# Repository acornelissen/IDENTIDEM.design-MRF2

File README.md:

# IDENTIDEM.design M(edium Format) (R)ange(F)inder Two (MRF2)

MRF2 is version two of an open hardware / open firmware medium-format rangefinder camera for **Mamiya Press / Universal Press lenses**. It combines custom PCBs, ESP32-S3 firmware, LiDAR-based lens coupled focusing, dual OLED displays, and printed mechanical parts so you can build a fully featured medium-format shooter with configurable lens profiles and film formats.

It is based on the [Panomicron Thulium](https://www.panomicron.com/thulium) designed by Oscar Oweson, has been heavily modified, but has kept the best ideas from that camera.

Keep checking back regularly as I keep making improvements as I use my own copy of this camera. 
You can [support me on Patreon](https://patreon.com/IDENTIDEMdesign), or just show me your builds and the photos you're making with the camera!

## Repo at a Glance

- `Firmware/` – ESP32-S3 Arduino firmware (full details in `Firmware/README.md`)
- `PCBs/` – KiCad projects + production Gerbers, in two supported revisions (see **Which board version?** below):
  - `PCBs/v2.0/` (MRF-Pro-v8) – adds a dedicated low-noise LiDAR regulator on the breakout, and reworks the main board's FPC power delivery and switch: v1 feeds the breakout one switched 3.3 V rail on FPC pins 1 and 6; v2 gives the LDO its own `VBAT` feed on pin 1 and adds full deterministic shutdown.
  - `PCBs/v1.0/` (MRF-Pro-v7.5) – simpler boards; great for short-range and landscape use.
  - Each revision holds `Main PCB/` (main board) and `Breakout/` (sensor breakout) sub-folders.
- `3MF/` – Print-ready 3MF files organized by part type (body, accessories, masks, fine parts)
- `STEP & F3D/` – Full assembly CAD (`MRF2-complete.f3d`) and shared STEP export (`MRF2-complete.step`)
- `OrcaSlicer/` – Slicer project files/profiles for printing

## Documentation Index

- `Documentation/flash-firmware/README.md` – Building and flashing the firmware on macOS, Linux, and Windows (VS Code or CLI)
- `Documentation/web-updater/README.md` – GitHub Pages browser updater architecture and deployment
- `Documentation/user-manual/USER_MANUAL.md` – On-device UI and calibration user manual
- `Documentation/wiring/README.md` – Power-switch/buttons and breakout-to-LiDAR harness wiring diagrams, for both board revisions
- `Firmware/README.md` – Firmware architecture, configuration, and CLI build commands

## Camera Features

- "LiDAR" distance measurement for accurate focus
- Dual OLED UI: 128×128 main in-viewfinder display + 128×32 external status display
- Light meter & exposure calculation for multiple ISO values
- Lens coupled via a high-accuracy linear position sensor
- Electronic frame counting using a rotary encoder
- Battery monitoring and on-device configuration, like in-camera lens calibration

## Which board version: v1 or v2?

Two board revisions are supported, and **the latest firmware runs on both, unchanged** — there are no board-specific builds, pin maps, or config flags. Connectors, sensors, displays, optics, printed parts, and the main board's component placement and outline are common to both, **but the main board's LiDAR power delivery was significantly reworked, alongside the breakout hardware.** On v1 the breakout runs entirely off one rail: the Feather's 3.3 V leaves the main board through the J4 power switch and comes back on FPC pins 1 and 6, so the LiDAR's laser supply, its logic supply and the STEMMA QT bus all hang off the same undecoupled net. That is the laser-pulse brownout this respin fixes. v2 splits the rails: pin 1 carries `VBAT` straight to the breakout's own LDO, and pin 6 stays the switched `3.3OUT` that gates it. Choose by the LiDAR range you need:

| | **v1 — MRF-Pro-v7.5** (`PCBs/v1.0/`) | **v2 — MRF-Pro-v8** (`PCBs/v2.0/`) |
| --- | --- | --- |
| Breakout | Bare — just the three connectors | Same connectors **+ a dedicated LiDAR LDO** (8 extra SMD parts) |
| FPC power delivery (main board) | One rail for everything: switched Feather 3.3 V on **both** pins 1 and 6 | Two rails: pin 1 carries **`VBAT`** to the breakout's LDO, pin 6 carries the gated, switched **`3.3OUT`** that enables it |
| LiDAR power | Shared Feather 3.3 V rail, no decoupling at the sensor | Isolated low-noise 3.3 V regulated **at the sensor** (TLV75533 off VBAT) |
| LiDAR range | Good up close and at landscape distance; **falls off at mid distance and in bright ambient** | **Full rated range indoors and in shade; direct sun still caps range** (~3 m on a sunlit target — a sensor optics limitation, not power-related; no board revision or firmware fixes it) |
| Power switch (main board) | Basic on/off — single shared 3.3 V net through J4 | Reworked **J4 DPDT**, two independent poles (gate `3.3OUT`; hold MCU `EN` low) for full deterministic shutdown (≤1 µA off) — same connector, board outline, and component placement, traces rerouted |
| Build effort | **Lowest** — breakout is a bare board, no SMD assembly | A bit more — breakout is an SMD assembly job (JLCPCB BOM/CPL provided) |
| Best for | Portraits ~1–3 m and landscapes; the cheapest, easiest build | Full-range focus indoors and in shade, better (not unlimited) in direct sun — the fuller-featured build |

- **Pick v1** for the simplest, cheapest build if you mostly shoot within a few metres or at landscape distances. Its LiDAR range can still be improved with the [hand-solder decoupling stopgap](Documentation/hardware-errata/lidar-stage1-decoupling.md), a v1-only remedy that v2 builds in.
- **Pick v2** for the sensor's full distance range indoors and in shade, deterministic power-off, and a main board that actually delivers real power to the LiDAR breakout, at the cost of the extra SMD parts on the breakout. Direct bright sun still caps range on either revision — that's the sensor fighting solar infrared at its own wavelength, not a supply problem this board fixes. The [LiDAR power errata](Documentation/hardware-errata/README.md) explains the why, and [field test protocol](Documentation/hardware-errata/lidar-field-test.md) covers all three lighting conditions including direct sun.

Building either? See the **[wiring guide](Documentation/wiring/README.md)** for the power-switch/buttons harness and breakout-to-LiDAR harness diagrams, per revision.

## Build Path (high level)

1. **Order PCBs**: Pick your version (see [Which board version?](#which-board-version-v1-or-v2)), then upload the Gerbers from that revision's `Main PCB/Gerber` and `Breakout/Gerber` folders — the `.gbrjob` files go straight to most fabs. For v2, the breakout is also an assembly job (the LDO SMD parts); its JLCPCB BOM/CPL live in `PCBs/v2.0/Breakout/JLCPCB/`.
2. **Assemble electronics**: Populate the main and breakout boards with the BoM below (through-hole and SMT mix), attach the Feather ESP32-S3, and wire the displays/sensors via STEMMA QT/Qwiic where applicable.
3. **Print the body**: Slice/print the 3MF models (see `3MF/` and any profiles in `OrcaSlicer/`). Fit tolerances may depend on your printer and material.
4. **Load firmware**: Follow `Documentation/flash-firmware/README.md` (macOS/Linux/Windows, VS Code or CLI), then run first-time calibration.
5. **Integrate**: Install the PCBs and displays into the printed parts, route wiring, and verify focus/meters on the bench before loading film.

## Bill of Materials

Marketplace listings (Amazon/AliExpress) change frequently. Treat those links as examples and verify specs before ordering.

### Electronics

| Item | Qty | Notes | Example sources |
| --- | --- | --- | --- |
| Feather ESP32-S3 (Adafruit 5477) | 1 | Main MCU, MAX17048 fuel gauge, 4MB flash / 2MB PSRAM | [Adafruit](https://www.adafruit.com/product/5477) |
| MRF2 Main PCB | 1 | Use Gerbers in your chosen revision's `Main PCB/Gerber` (`PCBs/v2.0/` or `PCBs/v1.0/`) | Any fab |
| MRF2 Breakout PCB | 1 | Use Gerbers in your chosen revision's `Breakout/Gerber`. **v2 breakout is an SMD assembly job** (see the LDO parts below) | Any fab |
| B-type 8-pin FPC ribbon cable | 1 | Links main PCB to breakout | [Amazon](https://www.amazon.co.uk/sourcing-map-Ribbon-Flexible-Printer/dp/B0F4K1KMKR/) |
| 8-pin JST-SH cable | 1 | For power switch and buttons, 10cm should be plenty | [AliExpress Search](https://www.aliexpress.com/w/wholesale-8-pin-jst%252525252dsh-cable.html) |
| 6-pin JST-SH cable | 1 | Connect the LiDAR sensor to the breakout board - some cutting and soldering needed on the connector supplied with the sensor | [AliExpress Search](https://www.aliexpress.com/w/wholesale-6-pin-jst%252525252dsh-cable.html) |
| LiDAR DTS6012M | 1 | Distance sensing | [AliExpress search](https://www.aliexpress.com/wholesale?SearchText=DTS6012M+UART) |
| 404R10KL1.0 Linear-position sensor | 1 | Lens position sensor | [Newark](https://www.newark.com/tt-electronics-bi-technologies/404r10kl1-0/linear-motion-potentiometer-10kohm/dp/15M2426) |
| Light sensor BH1750 breakout (Adafruit 4681) | 1 | Lux readings | [Adafruit](https://www.adafruit.com/product/4681) |
| IMU MPU6050 breakout (Adafruit 3886) | 1 | Orientation | [Adafruit](https://www.adafruit.com/product/3886) |
| ADC ADS1015 breakout (Adafruit 1083) | 1 | Lens position | [Adafruit](https://www.adafruit.com/product/1083) |
| STEMMA QT Rotary Encoder (Adafruit 5880) | 1 | Film advance tracking | [Adafruit](https://www.adafruit.com/product/5880) |
| 1.12" 128×128 SH1107 OLED (Adafruit 5297) | 1 | Main display | [Adafruit](https://www.adafruit.com/product/5297) |
| 128×32 SSD1306 OLED (I2C) | 1 | External status display | [AliExpress search](https://www.aliexpress.com/w/wholesale-128x32-oled-display-ssd1306.html) |
| JST-SH/Qwiic/STEMMA QT cables | 6-8 (extras if you want to shorten / modify) | I2C daisy-chain and encoder | [Adafruit](https://www.adafruit.com/product/4210) |
| LiPo cell (3.7V, 820mAh) - 44 x 30.5 x 6.8 mm | 1 | **CHECK POLARITY** | [Amazon](https://www.amazon.co.uk/dp/B082152887) |
| 8mm momentary button | 2 | Select buttons | [Amazon](https://www.amazon.co.uk/dp/B07S1MNB8C) |
| 6mm DPDT slide switch | 1 | Power switch | [Amazon](https://www.amazon.co.uk/dp/B07H9VPK1J) |

### Components for custom PCBs — connectors

| Item | Qty | Notes | Example sources |
| --- | --- | --- | --- |
| 0.5mm pitch 8-pin FPC connector (FPC-05F-8PH20, C2856797) | 2 | One on the main PCB, one on the breakout | [JLCPCB](https://jlcpcb.com/partdetail/XUNPU-FPC_05F8PH20/C2856797) |
| SH 1.0mm 6-pin connector, **right angle** (ZX-SH1.0-6PWT, C7430448) | 1 | Breakout J7 — LiDAR sensor | [JLCPCB](https://jlcpcb.com/partdetail/Megastar-ZX_SH1_06PWT/C7430448) |
| SH 1.0mm 4-pin connector, **right angle** (ZX-SH1.0-4PWT, C7430446) | 1 | Breakout J6 — STEMMA QT | [JLCPCB](https://jlcpcb.com/partdetail/Megastar-ZX_SH1_04PWT/C7430446) |

Main board **J4 differs by revision** — pick the one that matches the board you are having fabbed:

| Board | Item | Example sources |
| --- | --- | --- |
| **v2** (MRF-Pro-v8) | SH 1.0mm 8-pin, **right angle** (ZX-SH1.0-8PWT, C7430450) | [JLCPCB](https://jlcpcb.com/partdetail/Megastar-ZX_SH1_08PWT/C7430450) |
| **v1** (MRF-Pro-v7.5) | SH 1.0mm 8-pin, **top entry** (ZX-SH1.0-8PLT, C7430457) | [JLCPCB](https://jlcpcb.com/partdetail/Megastar-ZX_SH1_08PLT/C7430457) |

> Mind the `LT` / `WT` suffix. `LT` is top entry (vertical), `WT` is right angle (side entry). They have different land patterns and will not solder onto each other's pads — JLCPCB's DFM check flags it as pins overhanging the pad. The cable is the same either way.

### v2 breakout only — dedicated LiDAR regulator

These SMD parts populate the v2 breakout's LDO (the extra cost/effort over v1). **v1's breakout has none of these** — it just carries the connectors above. Full design background is in the [LiDAR power errata](Documentation/hardware-errata/README.md).

| Ref | Part | LCSC | Role |
| --- | --- | --- | --- |
| U1 | TLV75533 LDO, SOT-23-5 | C404027 | Dedicated 3.3 V regulator for the LiDAR |
| Cin1 | 1 µF, 0402 | C52923 | LDO input decoupling |
| Cin2 | 10 µF, 0805 | C15850 | LDO input bulk |
| C1 | 47 µF, 1206 | C96123 | Laser-rail bulk (at the sensor's laser pin) |
| C2 | 1 µF, 0603 | C15849 | LDO output stability |
| C3 | 100 nF, 0402 | C1525 | High-frequency bypass |
| FB1 | 0 Ω jumper, 0805 | C17477 | Splits the logic/laser rails (fit a ferrite later if needed) |
| R1 | 100 kΩ, 0402 | C25741 | LDO enable pulldown (clean power-off) |

### Hardware

| Item | Qty | Notes | Example sources |
| --- | --- | --- | --- |
| Heat-set inserts | as needed | M2x4 & M3x4 | Local fasteners supplier |
| Countersunk screws | as needed | M2x4, M2x6, M3x6, M3x8 countersunk screws | Local fasteners supplier |
| M3x6 thumb screw | 1 | To hold the door closed | Local fasteners supplier |
| Steel rod - for door hinge | 1 | Cut to length: ~82mm | [Amazon](https://www.amazon.co.uk/HXJDAM-Stainless-Steel-Round-Diameter/dp/B0D2V6WB1Y) |
| 2-turn door handle spring | 1 | For advance lever auto-return | [Amazon](https://www.amazon.co.uk/dp/B076VRBT4M) |
| CSK8PP one-way bearing / sprag clutch | 1 | For advance lever, make sure inner and outer are keyed | [AliExpress Search](https://www.aliexpress.com/w/wholesale-CSK8PP.html) |
| Cold shoe | 1 | Mount on top | [Amazon](https://www.amazon.co.uk/Anwenk-Adapter-Bracket-Standard-Monitor/dp/B01MD29V3X) |
| 20x5x2mm bar magnets | as needed | 1 for the body, 1 for each mask you print | [Amazon](https://amzn.eu/d/ejitdei) |
| 5x2mm round magnets | 2 | 1 for the body, 1 for the key | [Amazon](https://www.amazon.co.uk/100PCS-Magnets-Neodymium-Whiteboards-Picture/dp/B09H2W3TQZ) |

### Optics

| Item | Qty | Notes | Example sources |
| --- | --- | --- | --- |
| 20.0mm Dia. x 70.0mm FL plano-convex lens (PCX) | 1 | Rear viewfinder lens | [Edmund Optics](https://www.edmundoptics.co.uk/p/200mm-dia-x-700mm-fl-uncoated-plano-convex-lens/2705) |
| 25.0mm Dia. x -25 FL plano-concave lens (PCV) | 1 | Front viewfinder lens | [Edmund Optics](https://www.edmundoptics.co.uk/p/250mm-dia-x25-fl-uncoated-plano-concave-lens/5542/) |
| 30x30x1.1mm 50R/50T beam splitter | 1 | Sits between front and rear optics | [AliExpress Search](https://www.aliexpress.com/w/wholesale-30x30x1.1-50R%25252F50T-beam-splitter.html) |

## Cost Estimate (ballpark)

Assumes single-quantity retail buys (Adafruit/Amazon/AliExpress), optics from Edmund Optics, and a rough USD/GBP conversion; excludes shipping/VAT/import and assembly labor.

- Electronics (MCU, sensors, displays, cables, LiPo, switches): ~$125 / ~£100
- PCB share (DIY assembly; amortized per build): ~$10 / ~£6  \[full 5× PCB batch ~ $35 / £28\]
- Hardware/fasteners/mech bits: ~$25 / ~£20
- Optics (lenses + beam splitter): ~$115 / ~£90
- Printed parts material: ~$25 / ~£20
- Rough per-build total: ~$300 / ~£235 (add shipping/taxes and any PCB batch overhead you keep)

## CAD & Printed Parts

- Full assembly in `STEP & F3D/MRF2-complete.f3d` (Fusion 360) and `MRF2-complete.step` (generic).
- Print-ready 3MFs are grouped by function under `3MF/`. Use provided slicer profiles in `OrcaSlicer/` as a starting point and tweak for your printer/material.

## PCB Notes

- Open the KiCad projects for your revision: **v2** `PCBs/v2.0/Main PCB/KiCAD/MRF-Pro-v8.kicad_pro` + `PCBs/v2.0/Breakout/KiCAD/MRF-Pro-v8-breakout.kicad_pro`; **v1** `PCBs/v1.0/Main PCB/KiCAD/MRF-Pro-v7.5.kicad_pro` + `PCBs/v1.0/Breakout/KiCAD/MRF-Pro-v7.5-breakout.kicad_pro`.
- Fabrication: the provided Gerber sets include copper, mask, paste, silkscreen, drills, and a `.gbrjob` for auto-detection at most PCB fabs.
- Revs: `PCBs/v2.0/` (`MRF-Pro-v8`) adds the dedicated LiDAR LDO on the breakout and reworks the main board's LiDAR power delivery: v1 carries the whole breakout on one switched 3.3 V net (`3V3_SW`, out of J4 onto FPC pins 1 and 6); v2 rewires them to `VBAT`/`3.3OUT` and splits the J4 switch into a DPDT for full deterministic shutdown (same component placement and board outline, traces rerouted). `PCBs/v1.0/` (`MRF-Pro-v7.5`) is the simpler, unfixed original design. See [Which board version?](#which-board-version-v1-or-v2) and the [LiDAR power errata](Documentation/hardware-errata/README.md) for the design background.

## Firmware

Firmware source and build instructions live in `Firmware/README.md`. PlatformIO is used for builds/flash/monitoring. Calibrate lenses and film formats after first flash.

For browser-based updates, use the GitHub Pages firmware updater:
`https://update.mrf2.com/`

If a user reports the updater hanging (for example at "Preparing installation"), enable hidden debug mode by adding `?debug=1`:
`https://update.mrf2.com/?debug=1`

Then:
1. Reproduce the issue.
2. Click **Copy Debug Report**.
3. Send the JSON report back for diagnosis.

## License

Firmware and design files are released under the GNU GPL v3.0 (see `LICENSE`).

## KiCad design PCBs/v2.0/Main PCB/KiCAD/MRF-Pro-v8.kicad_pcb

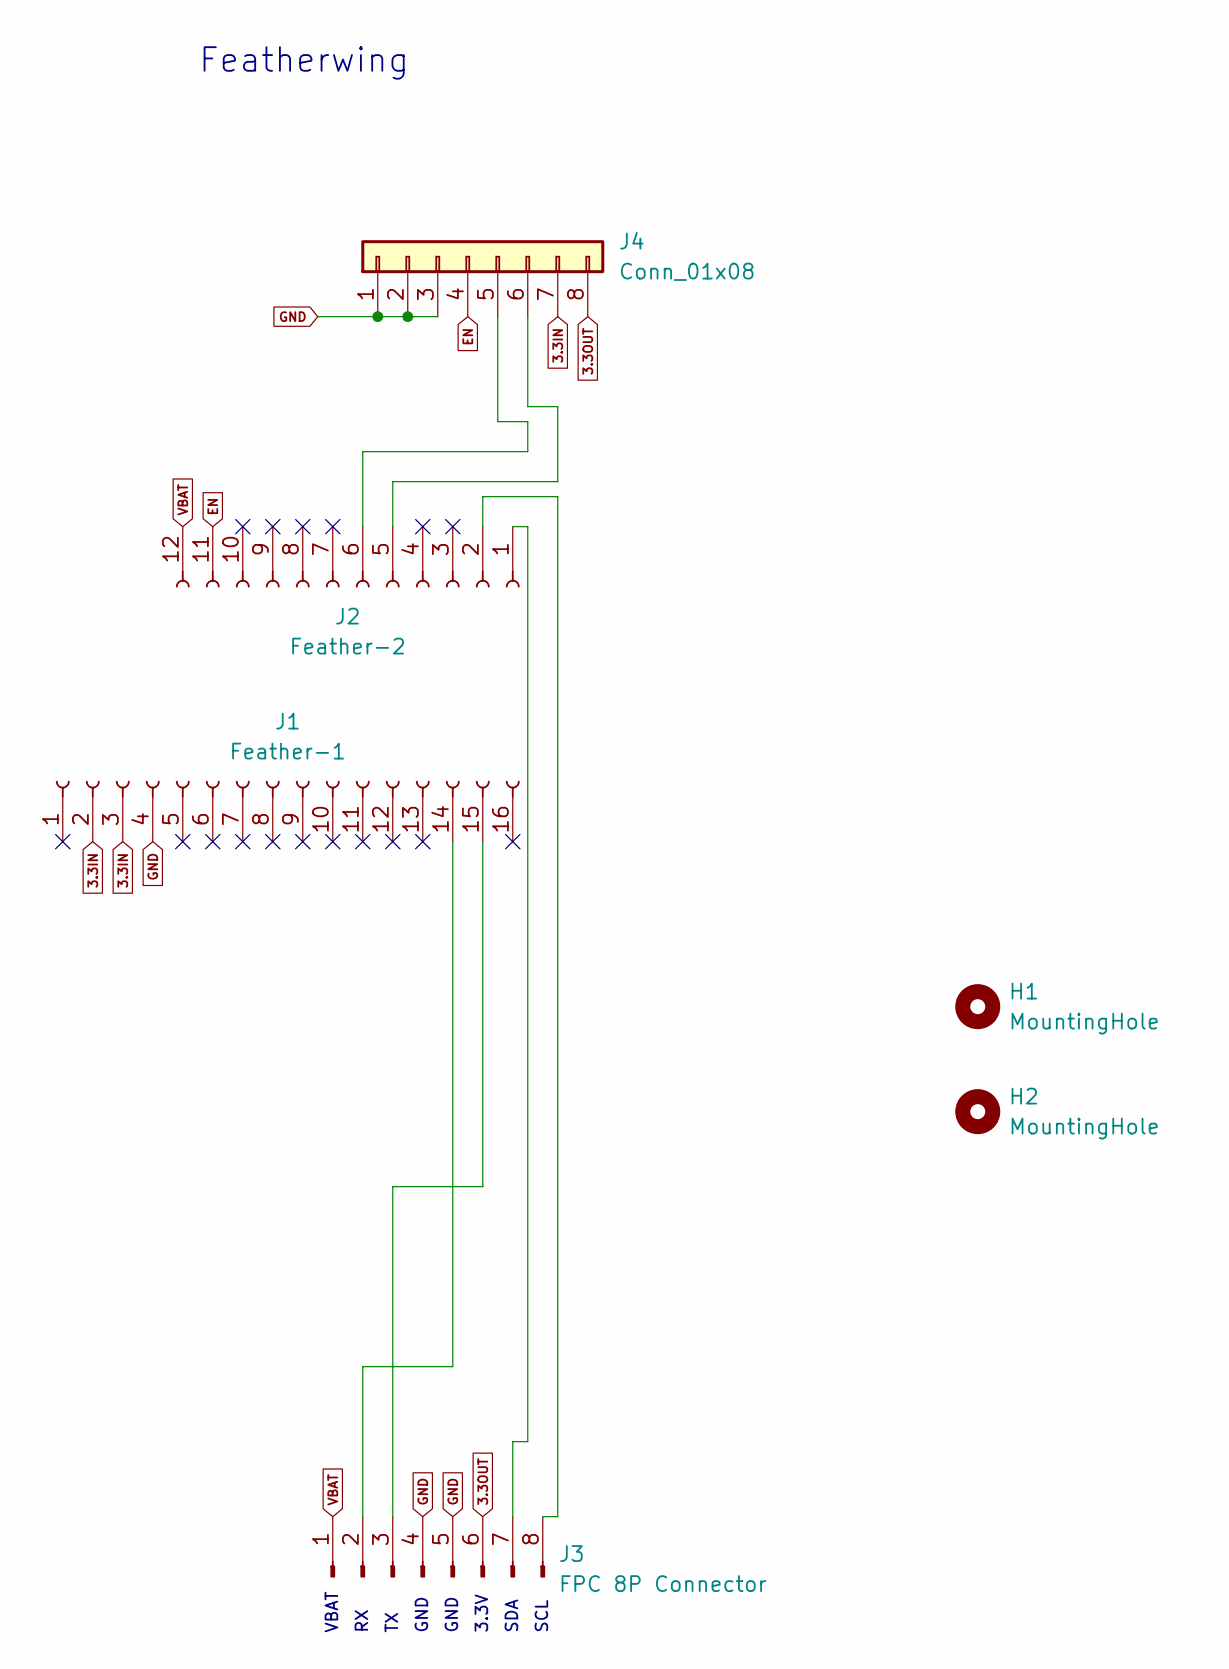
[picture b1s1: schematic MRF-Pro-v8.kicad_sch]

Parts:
H1, H2: MountingHole; MountingHole_2.2mm_M2
J1: Feather-1; PinHeader_1x16_P2.54mm_Vertical
J2: Feather-2; PinHeader_1x12_P2.54mm_Vertical
J3: FPC 8P Connector; TE_0-1734839-8_1x08-1MP_P0.5mm_Horizontal; LCSC C2856797
J4: Conn_01x08; JST_SH_SM08B-SRSS-TB_1x08-1MP_P1.00mm_Horizontal; LCSC C7430450

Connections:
3.3IN: J1.2, J1.3, J4.7
3.3OUT: J3.6, J4.8
EN: J2.11, J4.4
GND: J1.4, J3.4, J3.5, J4.1, J4.2, J4.3
unnamed: J1.14, J3.2
unnamed: J1.15, J3.3
unnamed: J2.1, J3.7
unnamed: J2.2, J3.8
unnamed: J2.5, J4.6
unnamed: J2.6, J4.5
VBAT: J2.12, J3.1

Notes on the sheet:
SDA
GND
Featherwing
VBAT
3.3V
SCL

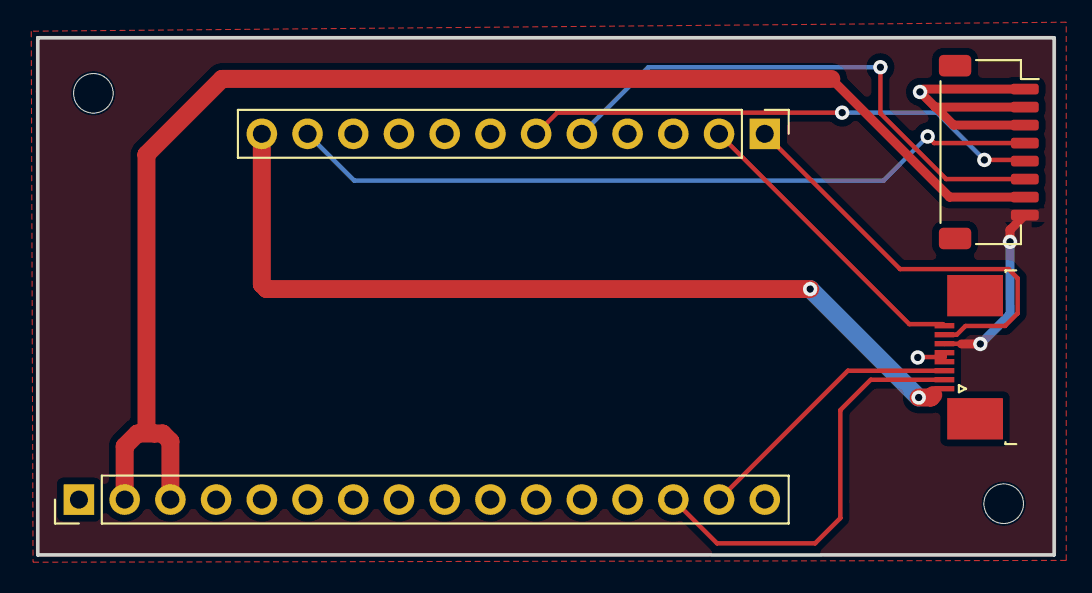
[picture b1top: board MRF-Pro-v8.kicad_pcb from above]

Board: 2 copper layers, 56.5 x 28.7 mm, 6 parts (0 on the bottom side), 11 nets.

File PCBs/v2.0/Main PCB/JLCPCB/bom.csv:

Designator,Footprint,Quantity,Value,LCSC Part #
J1,PinHeader_1x16_P2.54mm_Vertical,1,Feather-1,
J2,PinHeader_1x12_P2.54mm_Vertical,1,Feather-2,
J3,TE_0-1734839-8_1x08-1MP_P0.5mm_Horizontal,1,FPC 8P Connector,C2856797
J4,JST_SH_SM08B-SRSS-TB_1x08-1MP_P1.00mm_Horizontal,1,Conn_01x08,C7430450

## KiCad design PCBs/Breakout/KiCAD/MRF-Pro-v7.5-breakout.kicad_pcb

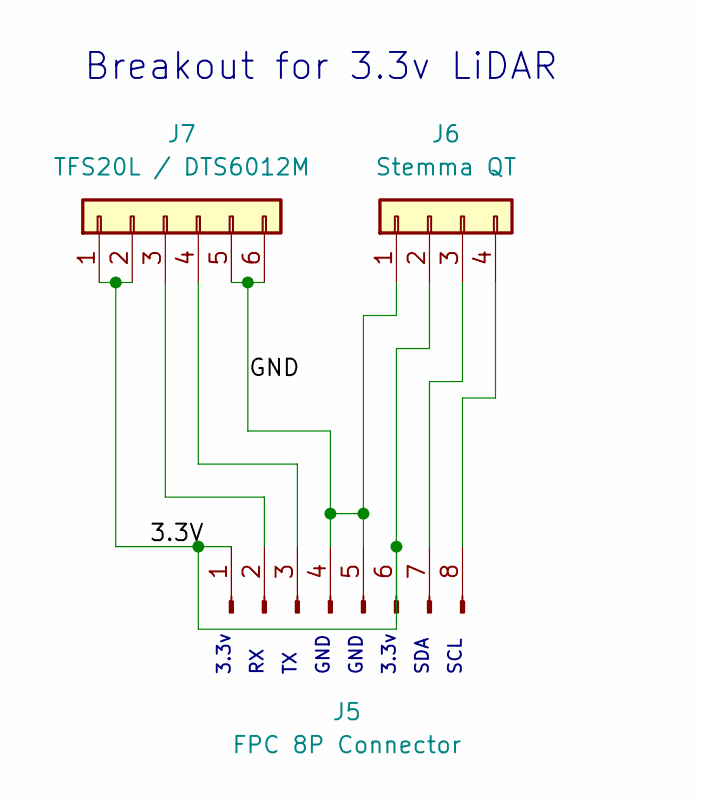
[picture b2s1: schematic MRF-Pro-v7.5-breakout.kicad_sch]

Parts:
J5: FPC 8P Connector; TE_0-1734839-8_1x08-1MP_P0.5mm_Horizontal; LCSC C2856797
J6: Stemma QT; JST_SH_SM04B-SRSS-TB_1x04-1MP_P1.00mm_Horizontal
J7: TFS20L / DTS6012M; JST_SH_SM06B-SRSS-TB_1x06-1MP_P1.00mm_Horizontal

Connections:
/3.3V: J5.1, J5.6, J6.2, J7.1, J7.2
/GND: J5.4, J5.5, J6.1, J7.5, J7.6
unnamed: J5.2, J7.3
unnamed: J5.3, J7.4
unnamed: J5.7, J6.3
unnamed: J5.8, J6.4

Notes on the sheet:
3.3v
SCL
GND
SDA
Breakout for 3.3v LiDAR

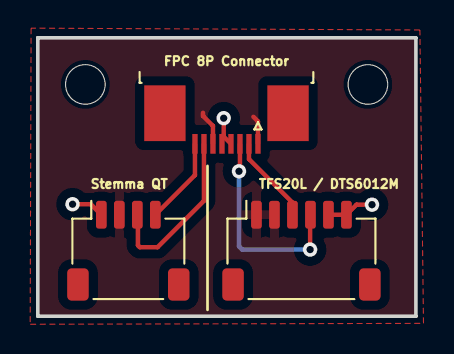
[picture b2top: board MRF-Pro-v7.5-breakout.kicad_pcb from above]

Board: 2 copper layers, 21.0 x 15.5 mm, 3 parts (0 on the bottom side), 6 nets.

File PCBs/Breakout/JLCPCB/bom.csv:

Designator,Footprint,Quantity,Value,LCSC Part #
J5,TE_0-1734839-8_1x08-1MP_P0.5mm_Horizontal,1,FPC 8P Connector,C2856797
J6,JST_SH_SM04B-SRSS-TB_1x04-1MP_P1.00mm_Horizontal,1,Stemma QT,C7430446
J7,JST_SH_SM06B-SRSS-TB_1x06-1MP_P1.00mm_Horizontal,1,TFS20L / DTS6012M,C7430448

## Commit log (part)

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2025-11-18 Initial project import (GPL-3.0)
2025-11-21 Update README with new video embed and thumbnail
    Added a new YouTube video iframe and thumbnail to the README.
2025-11-24 Highlight Mamiya Press lenses in README
    Emphasize 'Mamiya Press lenses' in the project description.
2025-12-19 Make LiDAR reads non-blocking
2025-12-20 Fix frameline sizing and trim format data
2025-12-21 Clamp out-of-range LiDAR distance display
2026-01-01 Fix LiDAR UI refresh after sleep
2026-01-08 Update magnet specifications in README
2026-01-26 Fix calibration UI highlights
2026-01-26 Improved and cleaned up all documentation.
2026-02-05 Stabilize lens ADC sampling and calibration
2026-02-08 Migrate DTS6012M integration to v2 API with CRC AUTO
2026-02-16 Add dual-target LiDAR fusion with staged calibration and confidence gating
2026-02-17 feat: add LiDAR quality indicator blocks on main UI
2026-02-17 fix: updater UX disables erase and emphasizes reboot
2026-02-17 ui: refine LiDAR quality indicator layout and docs
2026-02-17 Bump firmware to v9.6.0 and fix updater/counter regressions
2026-02-17 Add hidden web-updater debug mode and README instructions
2026-02-18 Add URL toggle to disable web-updater auto-retry
2026-02-19 Add LiDAR recovery and calibration quality guards
2026-02-19 Fix sleep edge cases and reposition EV readout in main UI
2026-02-21 Some small tweaks to CAD files. Updated 3MF and OrcaSlicer files accordingly.
2026-02-21 Rework setup menus and refresh user manual UI docs
2026-02-22 Relax LiDAR gating to reduce long-range dropouts
2026-02-22 Bump to 10.0.0 and refresh sleep/boot UI docs
2026-02-22 Add multi-version firmware selection to web updater
2026-02-22 Fix updater version selector loading state and cache busting
2026-02-22 Harden web updater serial port selection and error guidance
2026-02-22 Auto-switch Adafruit runtime USB ports to bootloader in updater
2026-02-22 Update web updater release notes and refresh manual UI docs
2026-02-22 Firmware 10.0.2: tune LiDAR bright-sun long-range gating
2026-02-24 CAD changes and exports for new mask. More tweaks to FFD.
2026-02-25 fix(firmware): release 10.1.2 lens-specific calibration scales
2026-02-26 feat(power): add adaptive lens film and meter polling
2026-02-26 refactor(ui): decompose interface rendering helpers
2026-02-26 docs: align LiDAR standby docs with runtime behavior
2026-02-26 fix(web-updater): sanitize FWVERSION parsing for release catalog
2026-02-27 Enable stricter source warning flags in PlatformIO
2026-02-28 Add GPIO wakeup infrastructure for device light sleep
    Adds the ESP-IDF headers and wakeup-source lifecycle to support
    esp_light_sleep_start() during device sleep mode.
    - Include esp_sleep.h and driver/gpio.h in loop_runtime.cpp.
    - enterSleepServices(): after CPU frequency scaling, configure
    BUTTON_LEFT_PIN and BUTTON_RIGHT_PIN as GPIO_INTR_LOW_LEVEL wakeup
    sources and enable the GPIO wakeup trigger. These stay configured
2026-02-28 docs(release): bump to 10.2.0 and refresh manuals/UI assets
    Update FWVERSION, README, user manual, CHANGELOG, and all UI SVG
    snapshots to reflect the 10.2.0 battery-savings release.
    - CHANGELOG: add 10.2.0 entry (light sleep, MPU/CPU scaling,
    polling cadences, sleep face, extended test suite).
    - web-updater-ui.svg: advance version labels and release notes panel.
    - sleep-ui.svg: redrawn to match new circle-face sleep indicator.
2026-02-28 refactor(setfuncs): lift LiDAR recovery and light meter statics to named structs
    Define LightMeterSmoothingState in the anonymous namespace and lift
    the LidarRecoveryState function-local static in setDistance() to a
    named namespace-scope instance. Replace all smoothingInitialized /
    smoothedLux locals in setLightMeter() with lightMeterSmoothing members.
    Behaviour is unchanged throughout.
2026-03-01 fix(sleep): always call checkButtons() regardless of wakeup cause
    GPIO_INTR_LOW_LEVEL fires when a button is pressed (pin goes LOW), but
    the release event (pin goes HIGH) arrives on the next timer wakeup, not
    a GPIO wakeup. The previous switch-case only called checkButtons() on
    GPIO wakeups, so Bounce2's rose() event — which registers activity and
    exits sleep — was never processed. Buttons were silent on wake.
    Fix: call checkButtons() unconditionally before the wakeup-cause
2026-03-01 fix(battery): recover batteryGaugeReady when begin() fails due to 0x36 conflict
    maxlipo.begin() returns false because the Seesaw (also at I2C address
    0x36) ACKs the soft-reset write that MAX17048 deliberately NACKs.
    i2c_dev is still valid after this failure, and the Seesaw's two-byte
    register protocol means it does not participate in MAX17048's
    single-byte register reads — so cellPercent() returns accurate data.
    After a failed begin(), attempt a SOC read and accept the gauge as
2026-03-14 fix(prefs): use targeted dirty masks in savePrefs() calls
    All cycle functions were calling savePrefs() without a dirty mask,
    defaulting to PREFS_DIRTY_ALL and causing unnecessary full NVS writes.
    Use PREFS_DIRTY_SETTINGS for settings changes to reduce flash wear.
2026-03-14 docs(release): update version references to 10.2.1
2026-03-14 Add breadcrumb headers to submenu screens
    Submenu titles now show the navigation path so users know where
    they are: "Setup > Film", "Setup > Lens", "Setup > Meter",
    "Setup > UI", and "Lens > Calibrate".
2026-03-14 Show current values inline on root Setup menu items
    Film, Lens, and Meter entries in the root Setup menu now display
    their active setting (e.g. "Film: 6x7 >", "Lens: 65/6.3 >",
    "Meter: ISO400 >") so users can check values without opening
    each submenu.
2026-03-14 Wrap calibration help text and improve error wording
    Split overflowing "(R) Cancel" onto its own line to fit the 128 px
    display, and replace "Turn ring further from camera" with the clearer
    "Increase focus distance". Update SVG, manual, and changelog.
2026-03-14 Expand focusing instructions and update docs for LiDAR tuning
    Add a full 'How to focus' section to the user manual covering the
    basic workflow, how to read the focus ring, and practical tips for
    sunlight, infinity, and parallax. Update CHANGELOG, README, and
    troubleshooting text for the relaxed LiDAR thresholds and extended
    fallback path.
2026-03-15 Hold calibration error messages on screen for minimum 2 seconds
    Calibration errors (unstable reading, out of sequence) could disappear
    before the user had time to read them. Track a timestamp when the
    error status is set and enforce a 2-second minimum display time:
    - inputs.cpp ignores new capture presses during the hold period
    - interface.cpp auto-clears the error once the hold expires
    - loop_runtime.cpp hashes the timestamp so the UI redraws on expiry
2026-03-15 Add compile-time validation for menu step constants
    Replace bare const int menu step indexes with plain enums that include
    a COUNT sentinel. static_assert checks that _MAX matches COUNT - 1,
    so adding a new menu item without updating the list is caught at
    compile time rather than silently wrapping to the wrong entry.
2026-03-15 Unify LiDAR display clearing into a single parameterised function
    clearLidarDisplay() in setfuncs.cpp and clearLidarUiForStandby() in
    loop_runtime.cpp did the same thing with different placeholder strings.
    Replace both with clearLidarDisplay(const char *placeholder) and
    remove the duplicate.
2026-03-15 Remove dead prev_bat_per and prev_lux globals
    prev_bat_per was written whenever bat_per changed but never read by
    any code path. prev_lux was similarly written in setLightMeter() but
    never consumed. Remove the declarations, definitions, and writes.
2026-03-15 Revert "Replace blocking LED pulse with non-blocking timed turn-off"
    This reverts commit 39527042a9b4bc5eda495d516026ac550fb2054a.
2026-03-15 Update docs for Factory Reset feature
    Add Factory Reset to changelog, user manual Health screen controls,
    firmware README Health screen description, and health-ui.svg footer.
2026-03-15 Inset calibration progress bar to align with text edges
    The progress bar was spanning the full 128px screen width while all
    text starts at X=3. Use CALIB_ITEM_X offset on both sides so the bar
    aligns with the text. Update calib-distance SVG and changelog.
2026-03-15 Add calibration complete SVG and update docs
    Add calib-complete.svg showing the full-screen success message.
    Reference it in the user manual calibration section and update the
    changelog to reflect the full-screen display with 1.5s hold.
2026-03-15 Add IDENTIDEM.design link to web updater footer
2026-03-15 Fix web updater colours and logo sizing to match identidem.design
    - Set panel background to solid white (was semi-transparent).
    - Use #f3f3f3 for secondary backgrounds matching the site.
    - Remove box shadows from panels for a cleaner flat look.
    - Shrink logo to 20px height, left-aligned with the page header.
    - Request 200px logo from CDN instead of 600px.
2026-03-15 Double logo size and increase CDN source resolution
2026-03-19 Set LiDAR frame rate to 50fps for improved far-range detection
    Lower frame rate gives the sensor more integration time per frame
    (~20ms vs ~4ms at 250fps), increasing photon collection for stronger
    return signals at distance. Applied after begin(), retry, and recovery.
2026-03-19 Update DTS6012M_UART library to v2.4.1 and align test stub
    Library v2.4.1 adds setFrameRate, getFilteredDistance, newDataAvailable,
    hasSecondaryTarget, getFirmwareVersion, setBaudRate, and a 128-byte
    circular buffer. Test stub updated to match new types and enum values.
2026-03-30 Fix lightmeter buffer overflow and update exposure display format
    Uncapped dtostrf into a 10-byte buffer caused overflow when exposure
    time reached very large second values. Cap added at 25 minutes.
    Display now shows seconds in 0.5s increments (1, 1.5, 2, 2.5 …) and
    switches to minutes+seconds (e.g. 1m30s) at one minute.
    Bump firmware version to 10.3.3.
2026-03-31 Reduce focus ring granularity to 5cm steps
    Compare lidar and lens distances in 5cm increments so the focus ring
    locks when the displayed values visually match, without snapping too
    early. Bump firmware to 10.3.5.
2026-04-08 Update docs and SVGs for v10.3.5 default changes and focus ring granularity
